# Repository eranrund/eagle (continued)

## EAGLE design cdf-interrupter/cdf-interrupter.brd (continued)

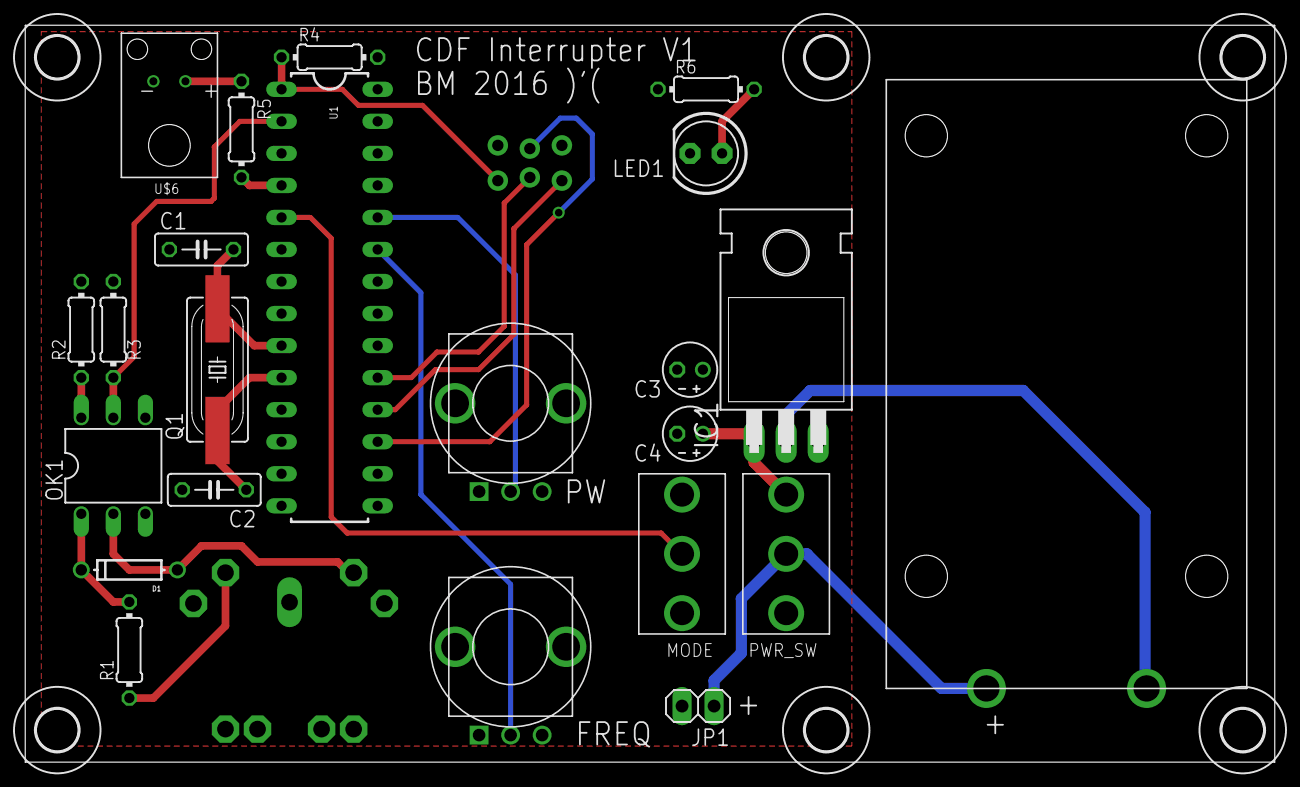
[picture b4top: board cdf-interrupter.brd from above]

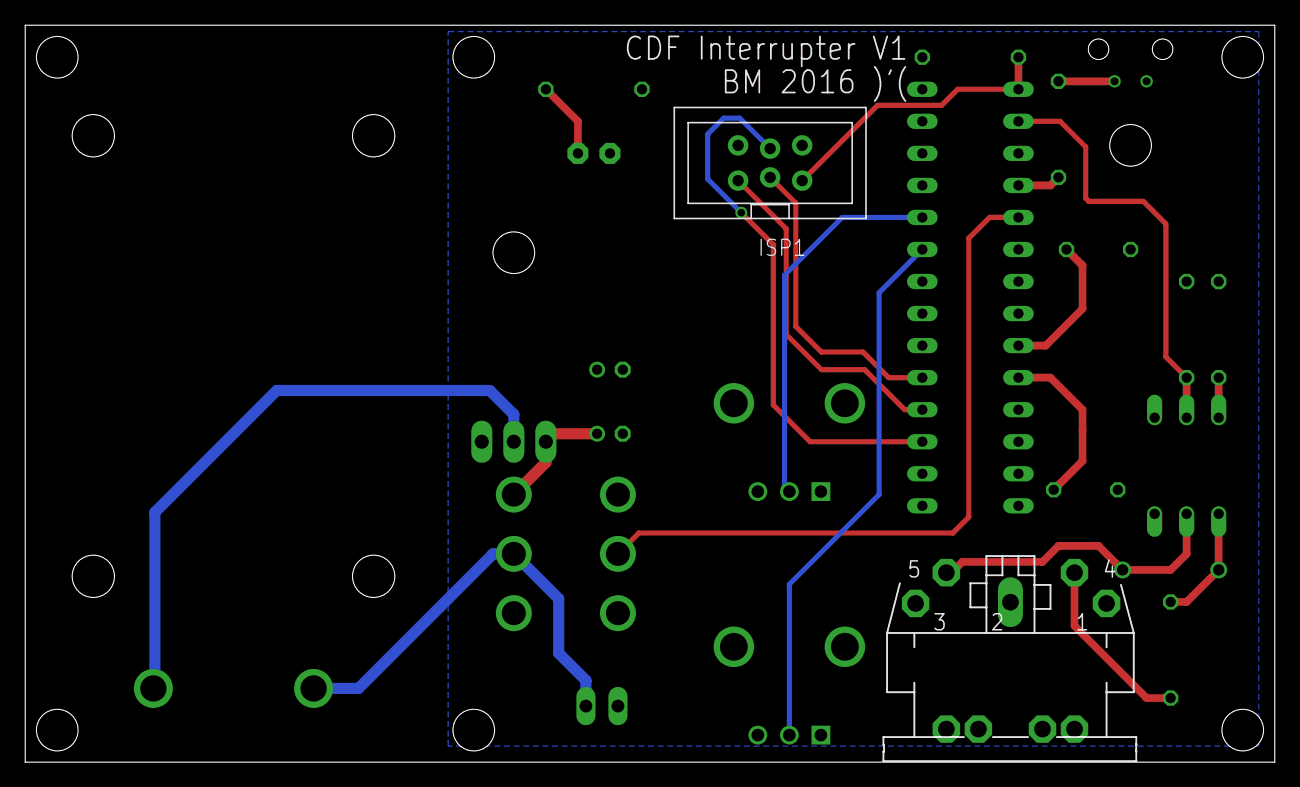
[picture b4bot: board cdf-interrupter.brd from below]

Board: 2 copper layers, 99.1 x 58.4 mm, 31 parts (2 on the bottom side), 21 nets.

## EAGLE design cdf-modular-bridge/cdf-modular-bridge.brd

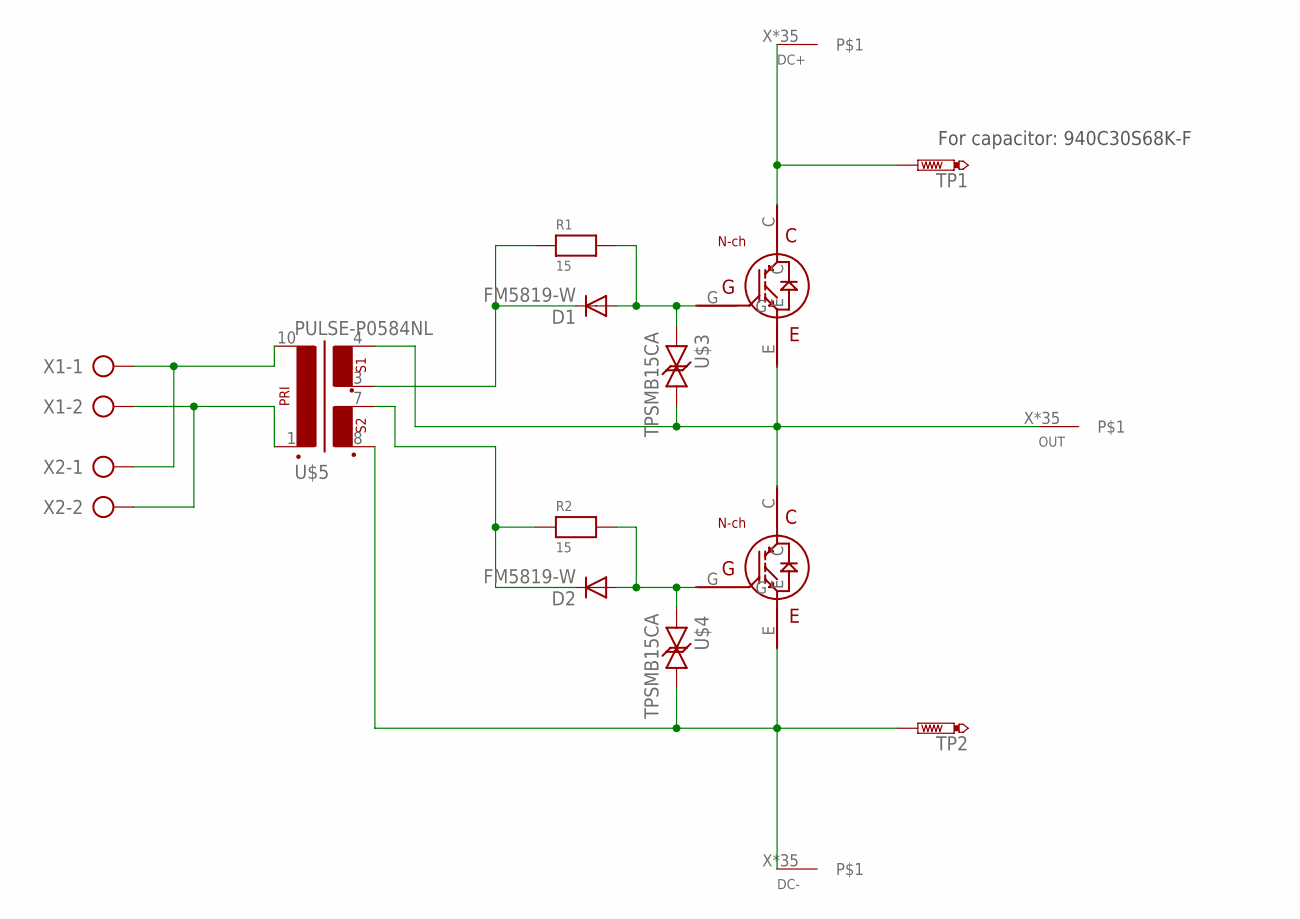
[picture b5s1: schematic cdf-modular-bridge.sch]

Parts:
D1, D2: FM5819-W; DO214AC
DC+: BIG-ASS-HOLE
DC-: BIG-ASS-HOLE
OUT: BIG-ASS-HOLE
R1, R2: 15; 1206
TP1, TP2: PTR1PAD1-17; P1-17
U$1, U$2: Ixgh48n60a3; IXGH40N60A
U$3, U$4: TPSMB15CA
U$5: PULSE-P0584NL
X1, X2: AK500/2

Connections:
DC+: DC+.X, DC+.X@1, DC+.X@2, DC+.X@3, DC+.X@4, DC+.X@5, DC+.X@6, DC+.X@7, DC+.X@8, DC+.X@9, DC+.X@10, DC+.X@11, DC+.X@12, DC+.X@13, DC+.X@14, DC+.X@15, DC+.X@16, DC+.X@17, DC+.X@18, DC+.X@19, DC+.X@20, DC+.X@21, DC+.X@22, DC+.X@23, DC+.X@24, DC+.X@25, DC+.X@26, DC+.X@27, DC+.X@28, DC+.X@29, DC+.X@30, DC+.X@31, DC+.X@32, DC+.X@34, DC+.X@120, TP1.TP, U$1.C
DC-: DC-.X, DC-.X@1, DC-.X@2, DC-.X@3, DC-.X@4, DC-.X@5, DC-.X@6, DC-.X@7, DC-.X@8, DC-.X@9, DC-.X@10, DC-.X@11, DC-.X@12, DC-.X@13, DC-.X@14, DC-.X@15, DC-.X@16, DC-.X@17, DC-.X@18, DC-.X@19, DC-.X@20, DC-.X@21, DC-.X@22, DC-.X@23, DC-.X@24, DC-.X@25, DC-.X@26, DC-.X@27, DC-.X@28, DC-.X@29, DC-.X@30, DC-.X@31, DC-.X@32, DC-.X@34, DC-.X@120, TP2.TP, U$2.E, U$4.P$2, U$5.8 (SEC2_POS)
unnamed: U$5.10 (PRI_NEG), X1.1, X2.1
unnamed: U$5.1 (PRI_POS), X1.2, X2.2
unnamed: D1.A, R1.2, U$1.G, U$3.P$1
unnamed: D2.A, R2.2, U$2.G, U$4.P$1
unnamed: D2.C, R2.1, U$5.7 (SEC2_NEG)
unnamed: D1.C, R1.1, U$5.3 (SEC1_POS)
OUT: OUT.X, OUT.X@1, OUT.X@2, OUT.X@3, OUT.X@4, OUT.X@5, OUT.X@6, OUT.X@7, OUT.X@8, OUT.X@9, OUT.X@10, OUT.X@11, OUT.X@12, OUT.X@13, OUT.X@14, OUT.X@15, OUT.X@16, OUT.X@17, OUT.X@18, OUT.X@19, OUT.X@20, OUT.X@21, OUT.X@22, OUT.X@23, OUT.X@24, OUT.X@25, OUT.X@26, OUT.X@27, OUT.X@28, OUT.X@29, OUT.X@30, OUT.X@31, OUT.X@32, OUT.X@34, OUT.X@120, U$1.E, U$2.C, U$3.P$2, U$5.4 (SEC1_NEG)

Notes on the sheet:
For capacitor: 940C30S68K-F

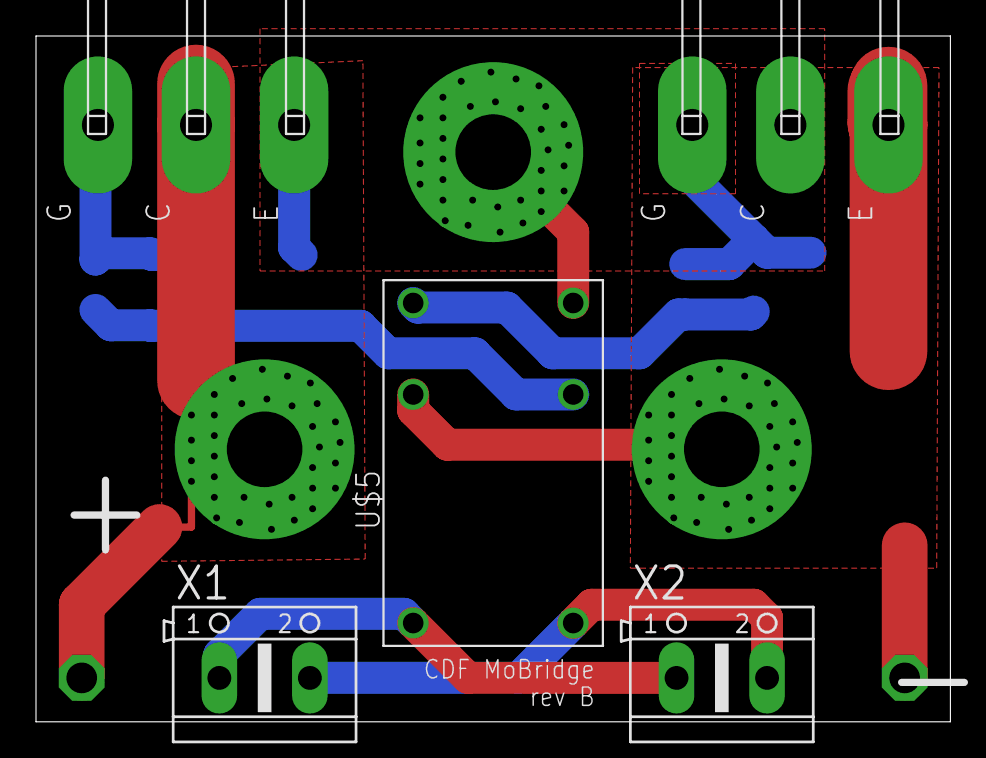
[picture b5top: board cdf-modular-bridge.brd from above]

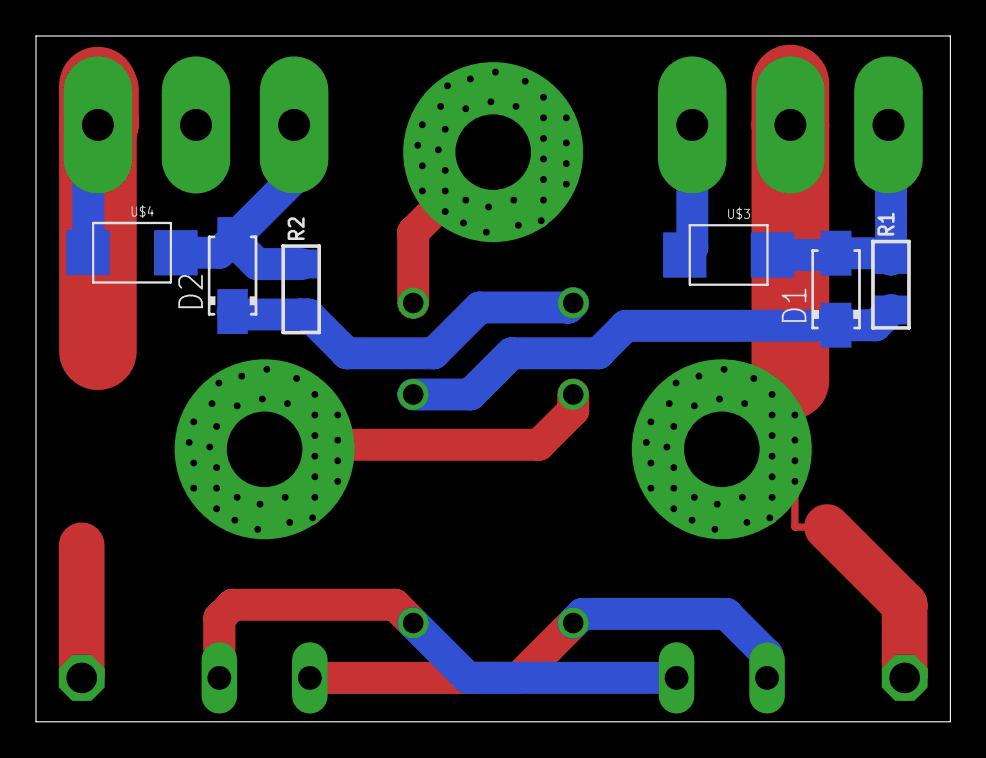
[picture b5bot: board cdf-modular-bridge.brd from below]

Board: 2 copper layers, 50.8 x 38.1 mm, 16 parts (6 on the bottom side), 9 nets.

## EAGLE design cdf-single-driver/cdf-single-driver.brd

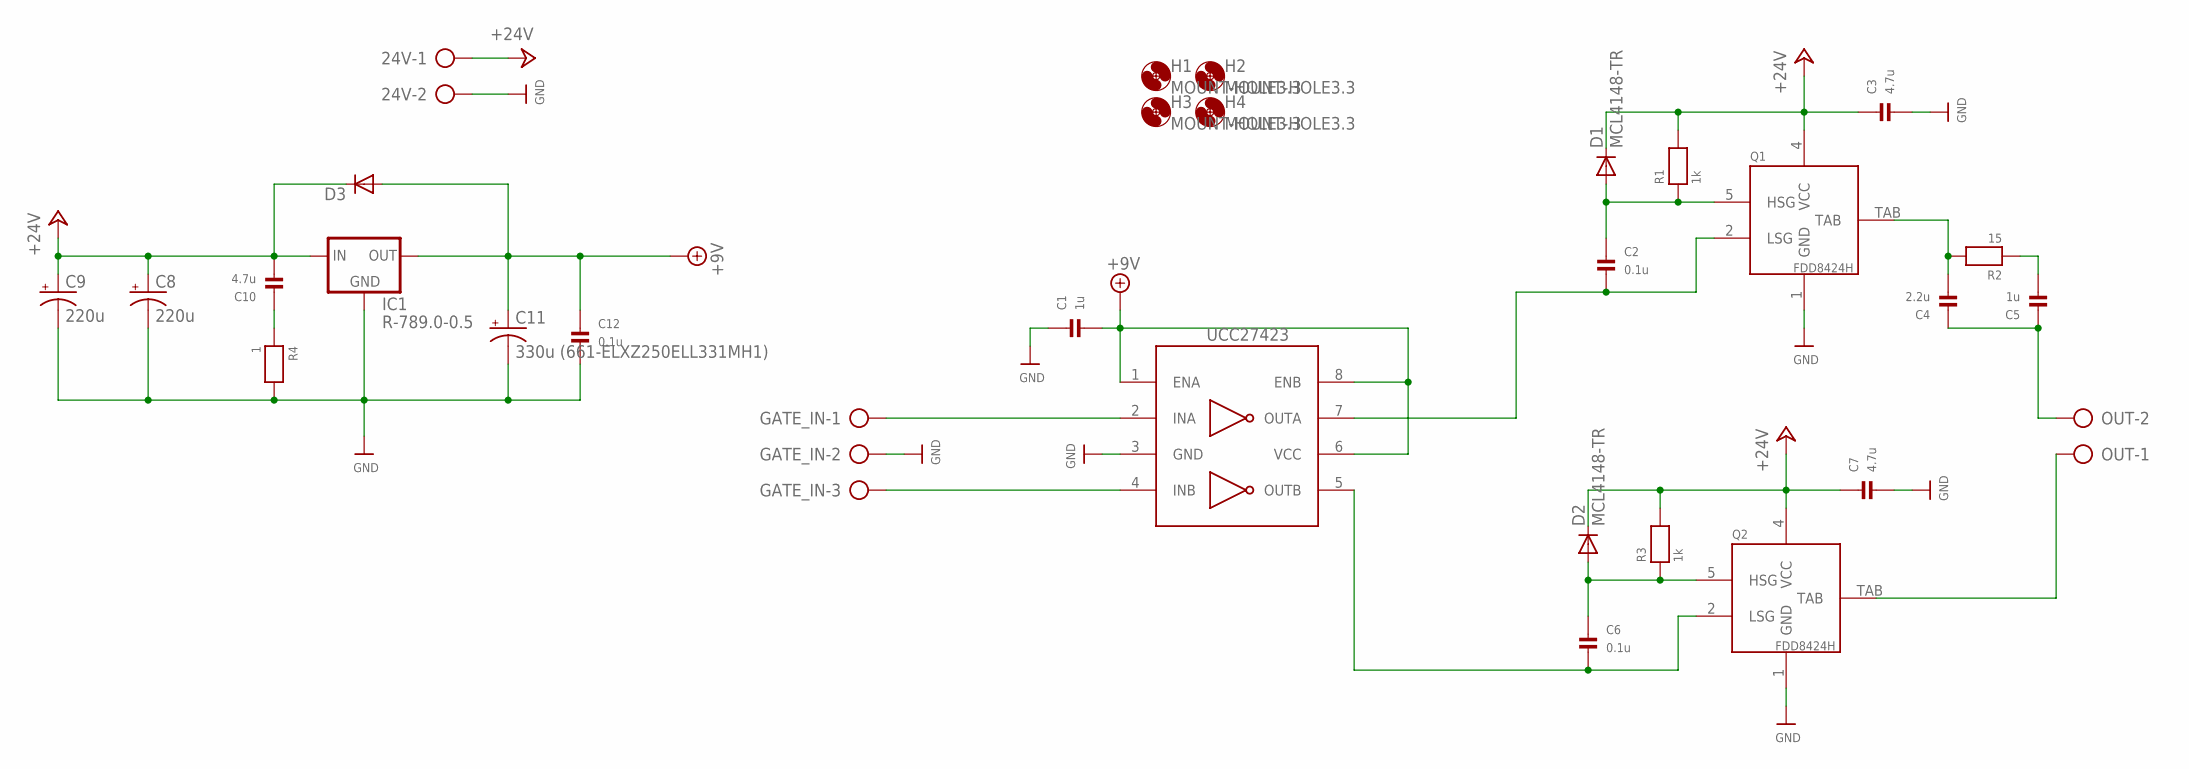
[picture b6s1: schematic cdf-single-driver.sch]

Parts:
24V: AK500/2
C1, C5: 1u; 0805
C2, C6, C12: 0.1u; 0805
C3, C7, C10: 4.7u; 0805
C4: 2.2u; 0805
C8, C9: 220u; E3,5-8
C11: 330u (661-ELXZ250ELL331MH1); E3,5-8
D1, D2: MCL4148-TR; MICROMELF-W
D3: DIODE-SOD123; SOD123
GATE_IN: AK500/3
H1, H2, H3, H4: MOUNT-HOLE3.3; 3,3
IC1: R-789.0-0.5; SIP3
IC2: UCC27423; SOIC8
OUT: AK500/2
Q1, Q2: FDD8424H; TO252-4
R1, R3: 1k; 0805
R2: 15; 0805
R4: 1; 0805

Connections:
+9V: C1.2, C11.+, C12.1, D3.A, IC1.3 (OUT), IC2.1 (ENA), IC2.6 (VCC), IC2.8 (ENB)
+24V: 24V.1, C3.1, C7.1, C8.+, C9.+, C10.2, D1.C, D2.C, D3.C, IC1.1 (IN), Q1.4 (VCC), Q2.4 (VCC), R1.2, R3.2
GND: 24V.2, C1.1, C3.2, C7.2, C8.-, C9.-, C11.-, C12.2, GATE_IN.2, IC1.2 (GND), IC2.3 (GND), Q1.1 (GND), Q2.1 (GND), R4.2
unnamed: GATE_IN.1, IC2.2 (INA)
unnamed: GATE_IN.3, IC2.4 (INB)
unnamed: C2.2, IC2.7 (OUTA), Q1.2 (LSG)
unnamed: C2.1, D1.A, Q1.5 (HSG), R1.1
unnamed: C4.2, Q1.TAB, R2.2
unnamed: C5.2, R2.1
unnamed: C4.1, C5.1, OUT.2
unnamed: C6.2, IC2.5 (OUTB), Q2.2 (LSG)
unnamed: C6.1, D2.A, Q2.5 (HSG), R3.1
unnamed: OUT.1, Q2.TAB
unnamed: C10.1, R4.1

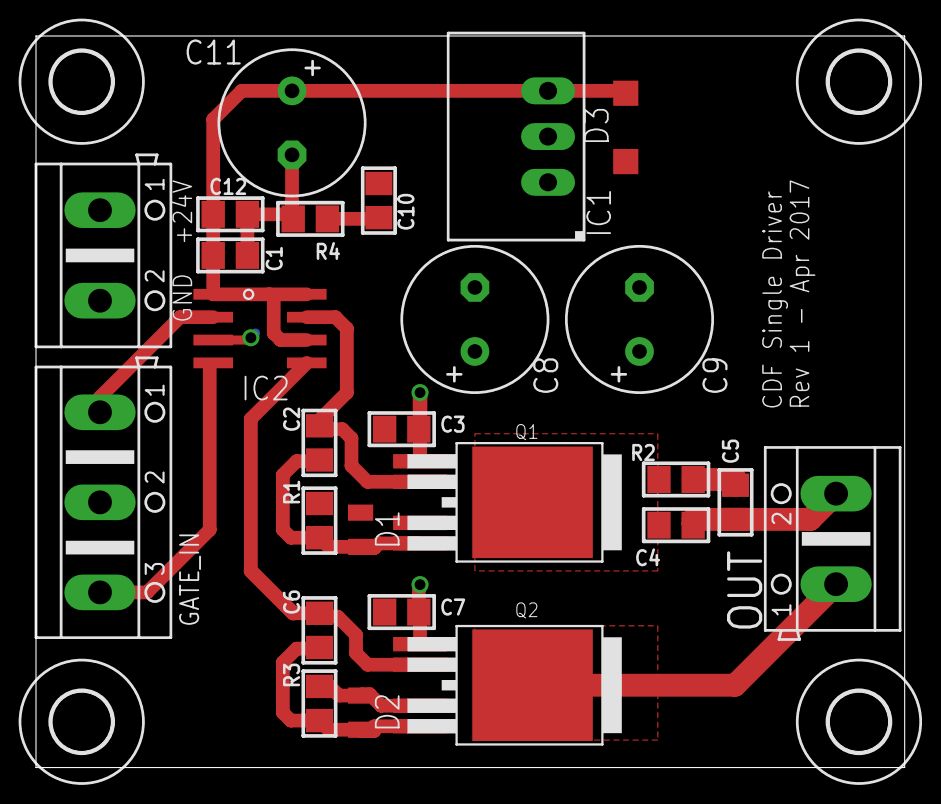
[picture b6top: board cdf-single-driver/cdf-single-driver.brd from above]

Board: 2 copper layers, 48.3 x 40.6 mm, 30 parts (0 on the bottom side), 14 nets.

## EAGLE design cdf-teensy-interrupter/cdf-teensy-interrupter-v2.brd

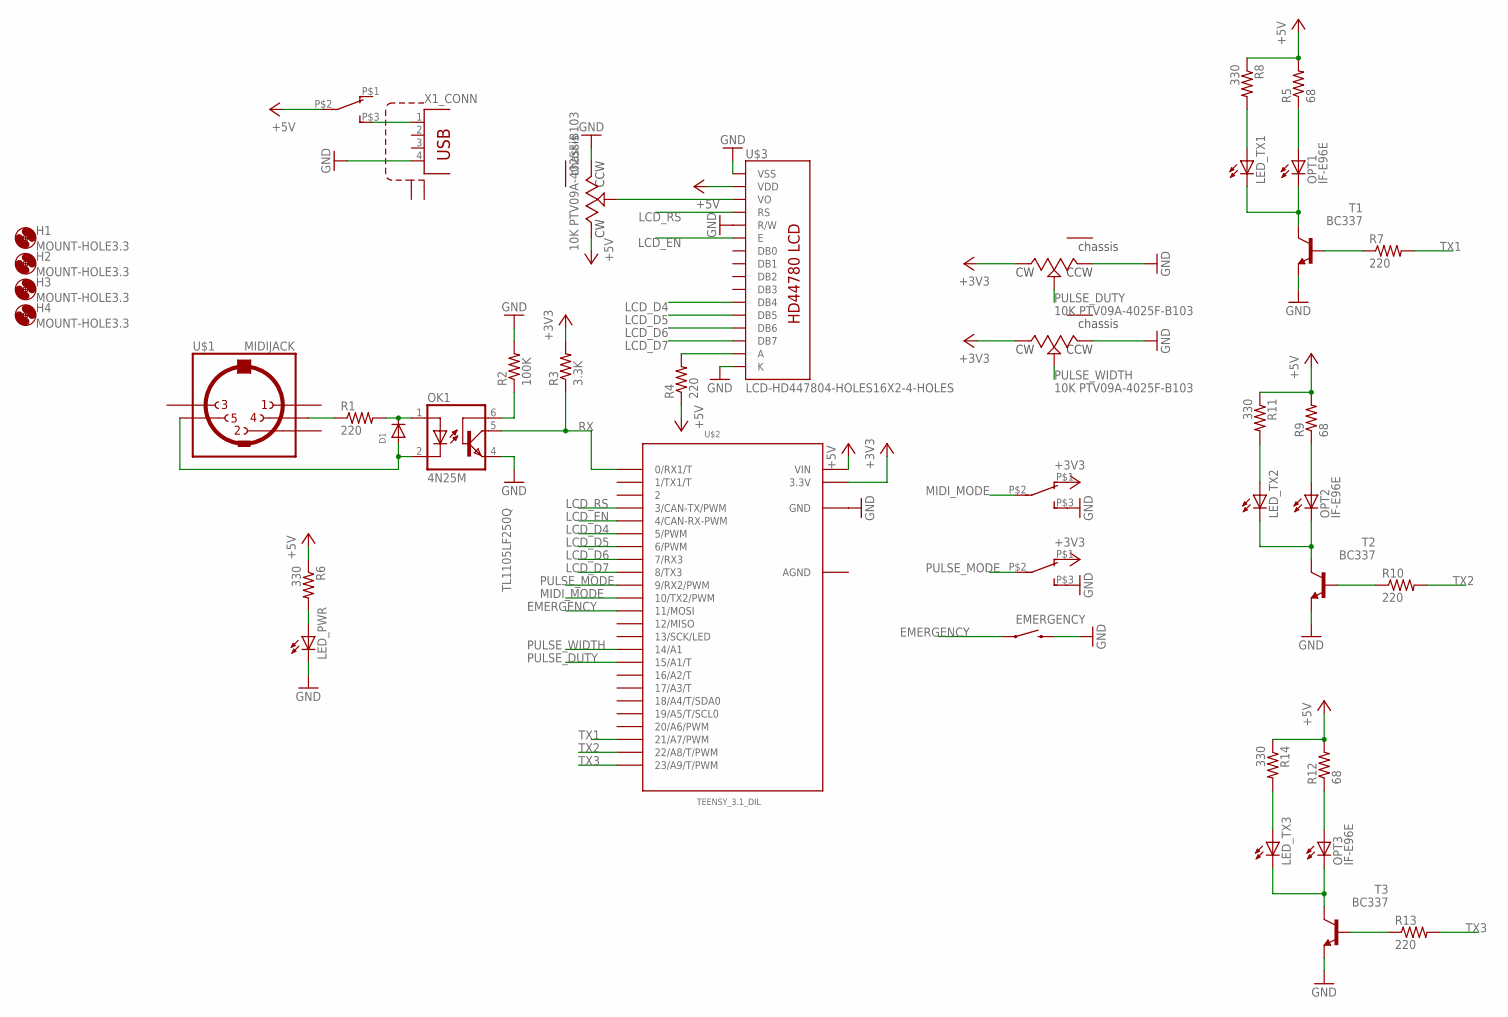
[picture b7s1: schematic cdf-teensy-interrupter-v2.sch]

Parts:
D1: DIODEDO-1N4148; DO-1N4148
EMERGENCY: TL1105LF250Q; TACTILE-PTH
H1, H2, H3, H4: MOUNT-HOLE3.3; 3,3
LCD_BL: 10K PTV09A-4025F-B103; PTV09A-4
LED_PWR: LED5MM
LED_TX1, LED_TX2, LED_TX3: LED5MM
MIDI: 100SP1T1B4M2QE
OK1: 4N25M; DIL06
OPT1, OPT2, OPT3: IF-E96E
PULSE: 100SP1T1B4M2QE
PULSE_DUTY: 10K PTV09A-4025F-B103; PTV09A-4
PULSE_WIDTH: 10K PTV09A-4025F-B103; PTV09A-4
PWR_SW: 100SP1T1B4M2QE
R1, R4, R7, R10, R13: 220; 0204/7
R2: 100K; 0204/7
R3: 3.3K; 0204/7
R5, R9, R12: 68; 0204/7
R6, R8, R11, R14: 330; 0204/7
T1, T2, T3: BC337; TO92
U$1: MIDIJACK; CP-2350
U$2: TEENSY_3.1_DIL; TEENSY3-DIL
U$3: LCD-HD447804-HOLES16X2-4-HOLES; LCD-16X2-4HOLES
X1: TE-292304-1

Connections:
+3V3: MIDI.P$1 (1), PULSE.P$1 (1), PULSE_DUTY.3 (CW), PULSE_WIDTH.3 (CW), R3.2, U$2.3.3V
+5V: LCD_BL.3 (CW), PWR_SW.P$2 (2), R4.1, R5.2, R6.1, R8.1, R9.2, R11.1, R12.2, R14.1, U$2.VIN, U$3.2 (VDD)
AGND: U$2.AGND
EMERGENCY: EMERGENCY.1, U$2.11 (11/MOSI)
GND: EMERGENCY.3 (2), LCD_BL.1 (CCW), LED_PWR.K (C), MIDI.P$3 (3), OK1.4 (EMI), PULSE.P$3 (3), PULSE_DUTY.1 (CCW), PULSE_WIDTH.1 (CCW), R2.2, T1.1 (E), T2.1 (E), T3.1 (E), U$2.GND, U$3.1 (VSS), U$3.5 (R/W), U$3.16 (K), X1.4
LCD_D4: U$2.5 (5/PWM), U$3.11 (DB4)
LCD_D5: U$2.6 (6/PWM), U$3.12 (DB5)
LCD_D6: U$2.7 (7/RX3), U$3.13 (DB6)
LCD_D7: U$2.8 (8/TX3), U$3.14 (DB7)
LCD_EN: U$2.4 (4/CAN-RX-PWM), U$3.6 (E)
LCD_RS: U$2.3 (3/CAN-TX/PWM), U$3.4 (RS)
MIDI_MODE: MIDI.P$2 (2), U$2.10 (10/TX2/PWM)
unnamed: R1.1, U$1.4
unnamed: D1.C, OK1.1 (A), R1.2
unnamed: D1.A, OK1.2 (C), U$1.5
unnamed: OK1.6 (BAS), R2.1
unnamed: LCD_BL.2 (WIPER), U$3.3 (VO)
unnamed: R4.2, U$3.15 (A)
unnamed: R7.1, T1.2 (B)
unnamed: OPT1.P$2_ANODE+ (A), R5.1
unnamed: LED_PWR.A, R6.2
unnamed: LED_TX1.A, R8.2
unnamed: LED_TX1.K (C), OPT1.P$1_CATHODE- (C), T1.3 (C)
unnamed: OPT2.P$2_ANODE+ (A), R9.1
unnamed: R10.1, T2.2 (B)
unnamed: LED_TX2.K (C), OPT2.P$1_CATHODE- (C), T2.3 (C)
unnamed: LED_TX2.A, R11.2
unnamed: OPT3.P$2_ANODE+ (A), R12.1
unnamed: R13.1, T3.2 (B)
unnamed: LED_TX3.K (C), OPT3.P$1_CATHODE- (C), T3.3 (C)
unnamed: LED_TX3.A, R14.2
unnamed: PWR_SW.P$3 (3), X1.1
PULSE_DUTY: PULSE_DUTY.2 (WIPER), U$2.15/A1 (15/A1/T)
PULSE_MODE: PULSE.P$2 (2), U$2.9 (9/RX2/PWM)
PULSE_WIDTH: PULSE_WIDTH.2 (WIPER), U$2.14/A0 (14/A1)
RX: OK1.5 (COL), R3.1, U$2.0 (0/RX1/T)
TX1: R7.2, U$2.21/A7 (21/A7/PWM)
TX2: R10.2, U$2.22/A8 (22/A8/T/PWM)
TX3: R13.2, U$2.23/A9 (23/A9/T/PWM)

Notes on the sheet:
TL1105LF250Q

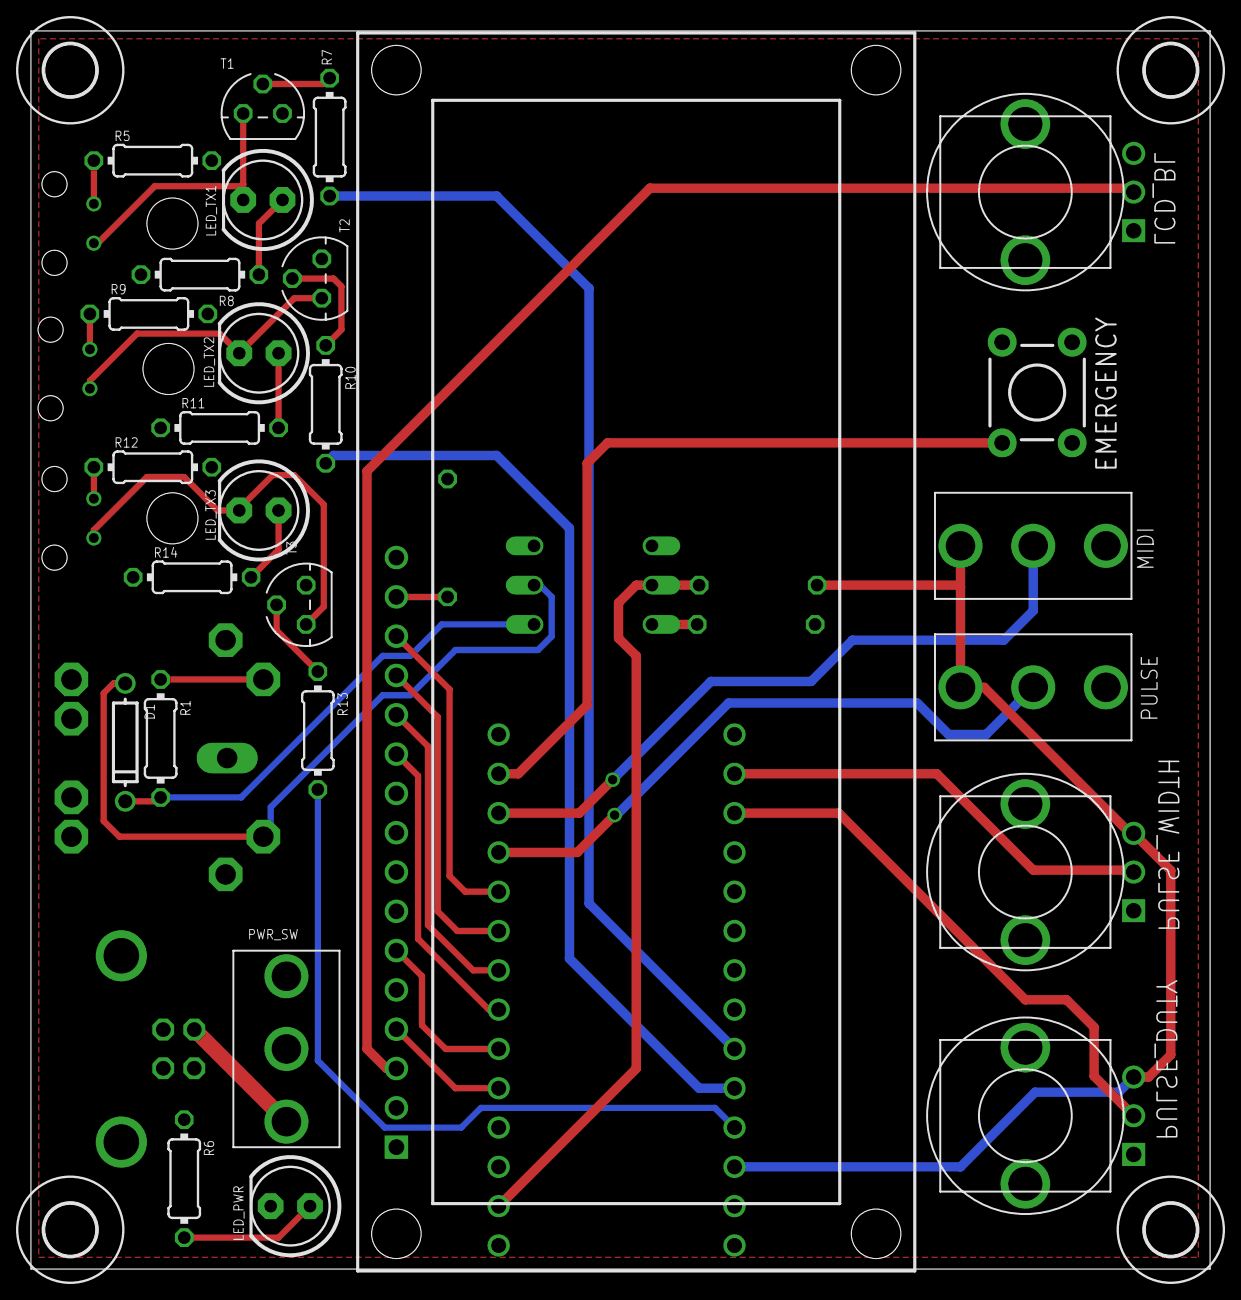
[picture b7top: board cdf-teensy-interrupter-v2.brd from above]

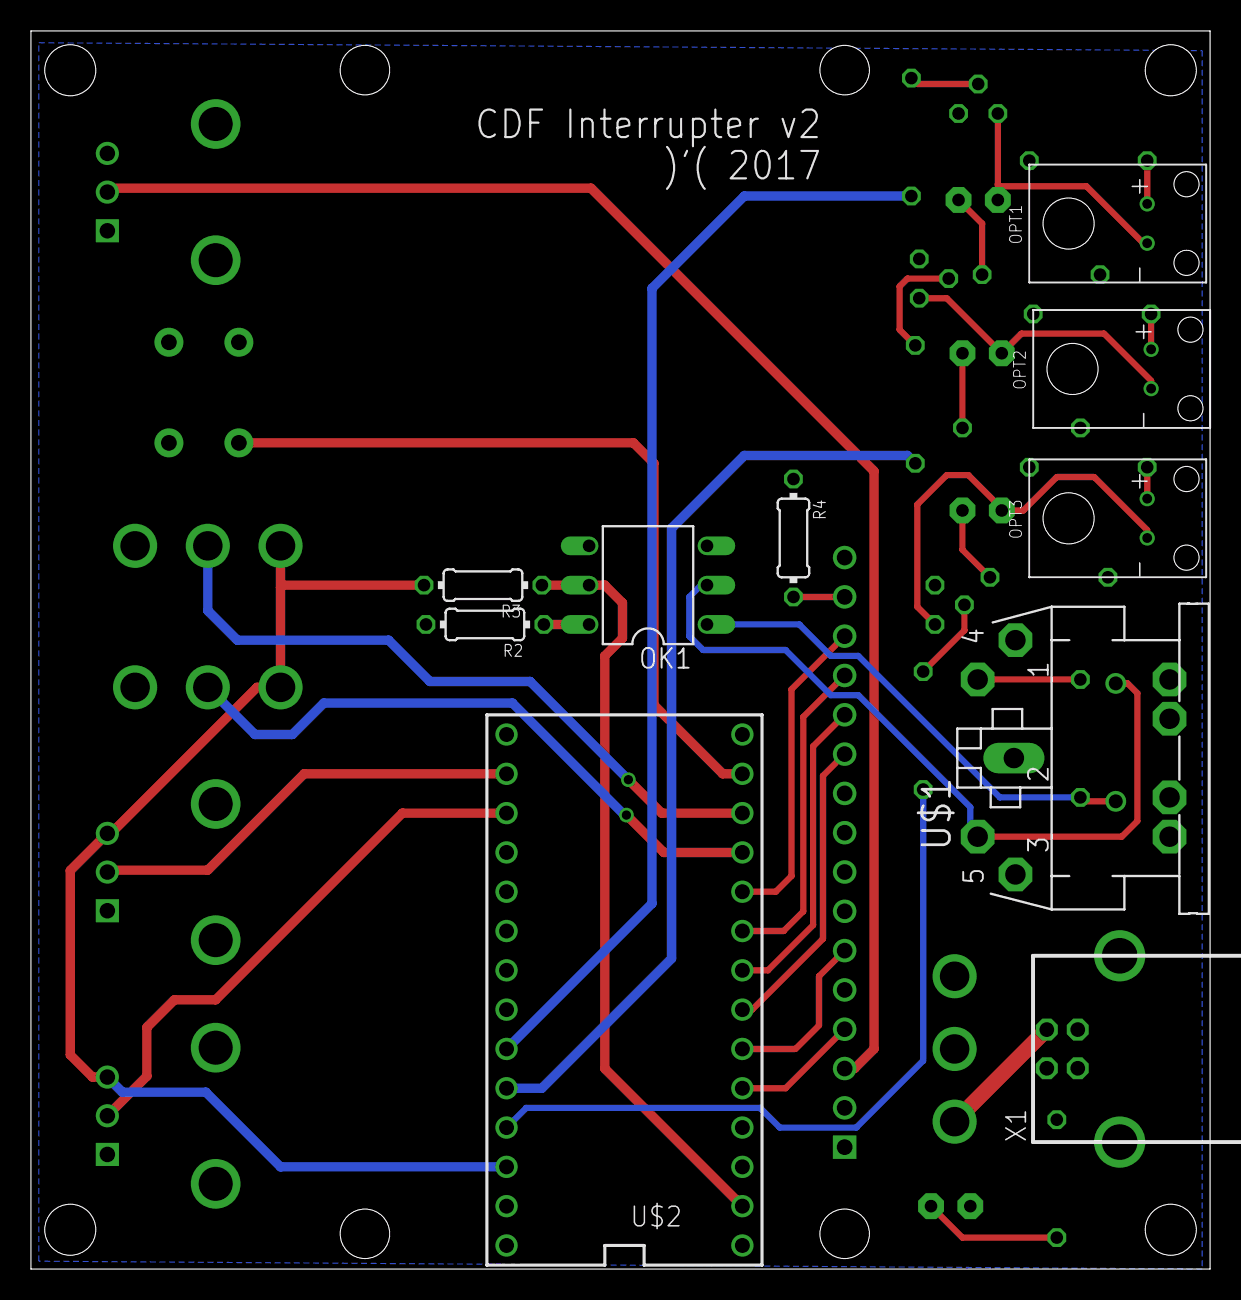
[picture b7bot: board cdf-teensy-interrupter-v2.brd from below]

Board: 2 copper layers, 76.2 x 80.0 mm, 41 parts (10 on the bottom side), 38 nets.
